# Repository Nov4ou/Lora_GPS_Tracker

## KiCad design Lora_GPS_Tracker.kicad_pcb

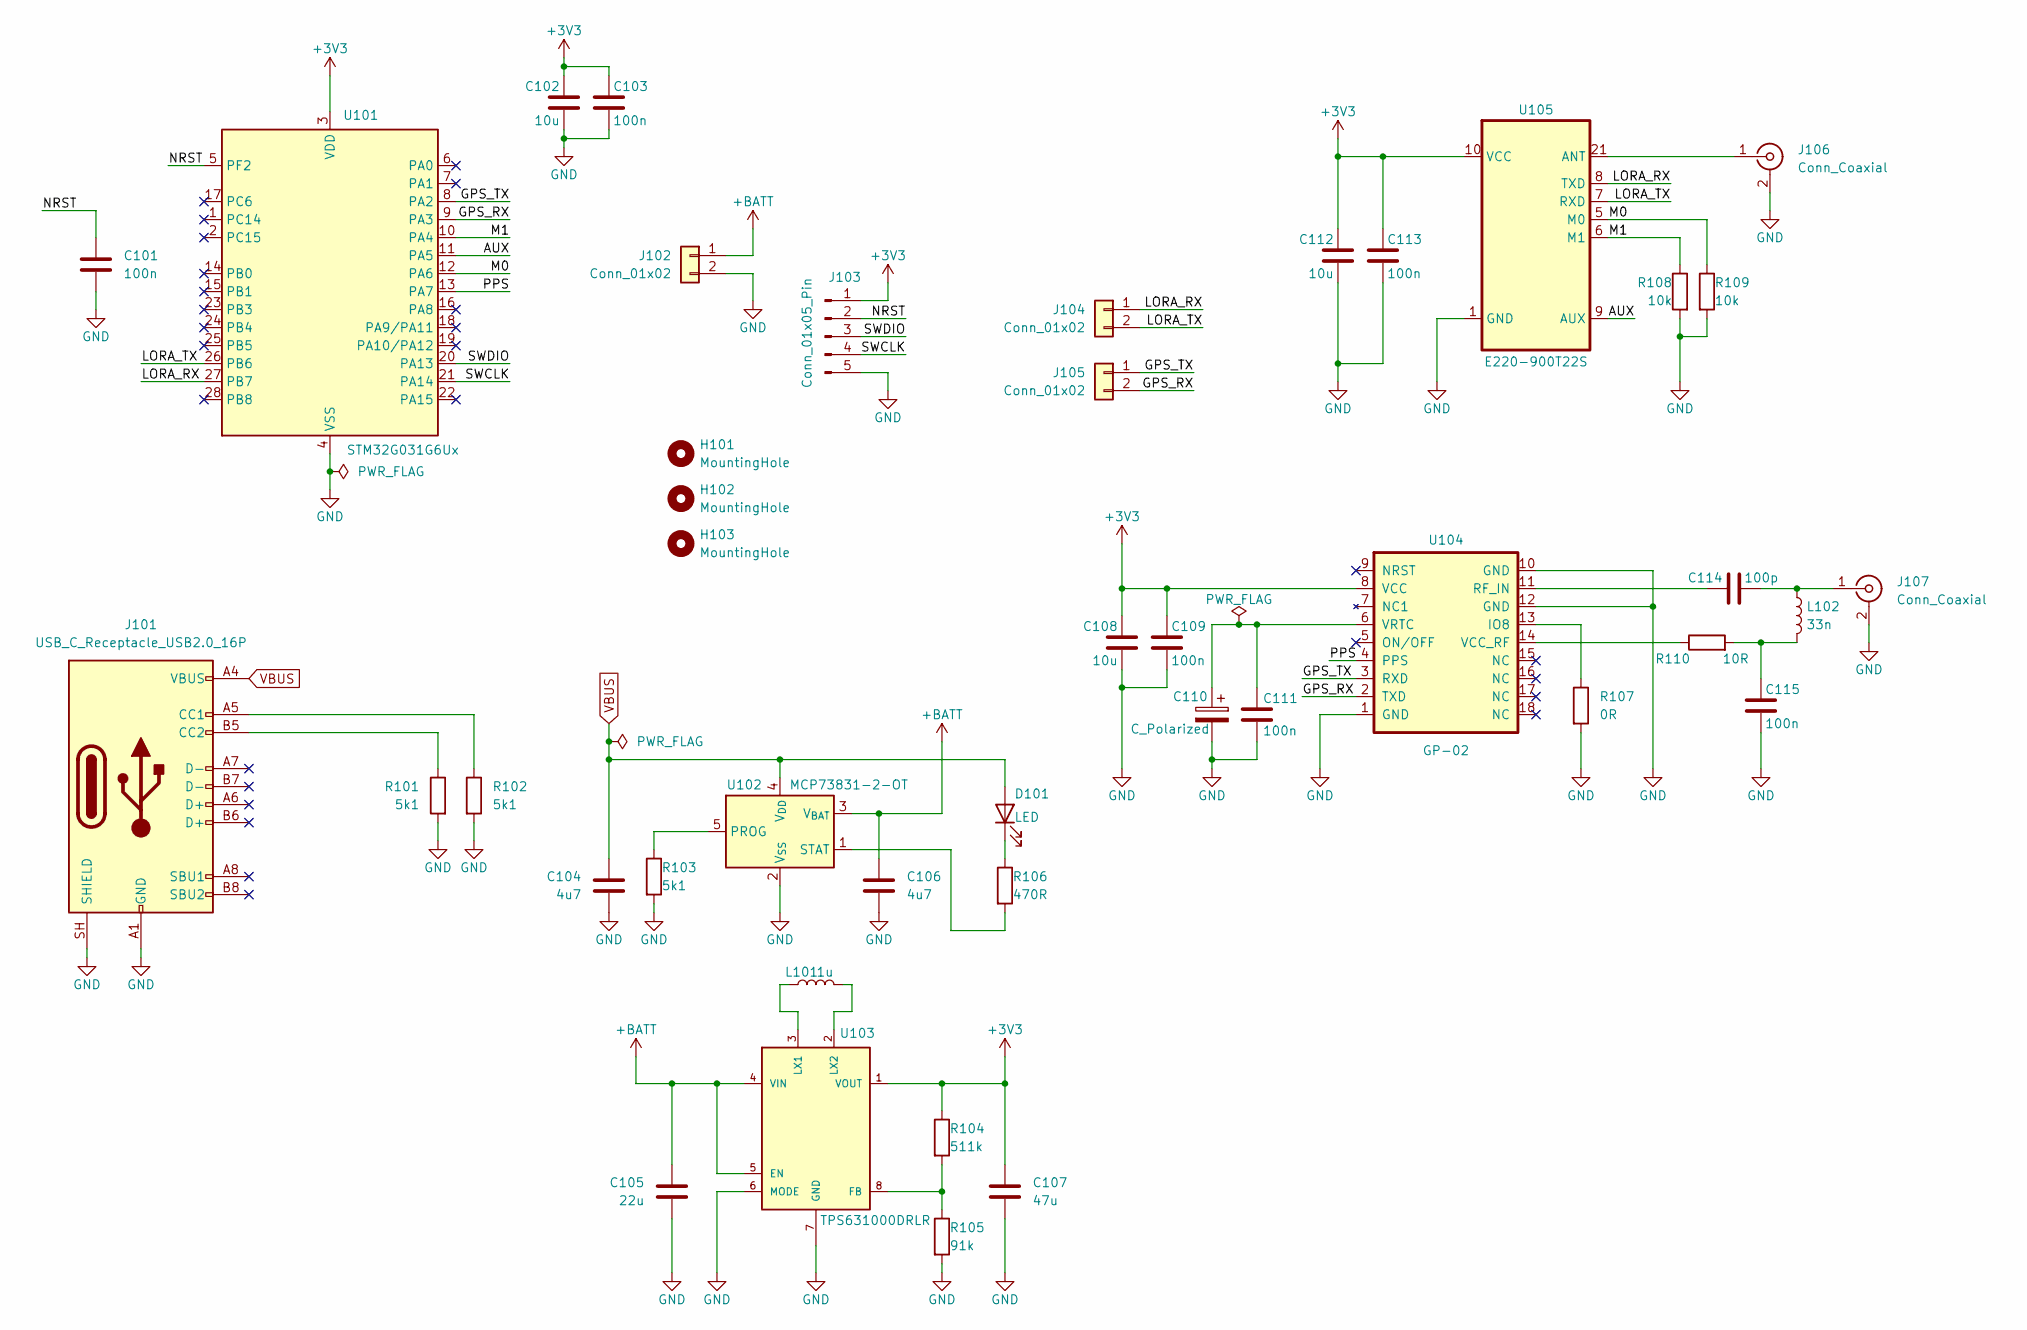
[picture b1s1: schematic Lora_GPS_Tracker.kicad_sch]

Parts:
C101, C103, C109, C111, C113, C115: 100n; C_0402_1005Metric
C102, C108, C112: 10u; C_0603_1608Metric
C104, C106: 4u7; C_0603_1608Metric
C105: 22u; C_0805_2012Metric
C107: 47u; C_0805_2012Metric
C110: C_Polarized; CAP-SMD_2P-L4.8-W4.8-TR
C114: 100p; C_0402_1005Metric
D101: LED; LED_0603_1608Metric
H101, H102, H103: MountingHole; MountingHole_2.2mm_M2
J101: USB_C_Receptacle_USB2.0_16P; USB_C_Receptacle_GCT_USB4105-xx-A_16P_TopMnt_Horizontal
J102: Conn_01x02; JST_PH_S2B-PH-K_1x02_P2.00mm_Horizontal
J103: Conn_01x05_Pin; PinHeader_1x05_P2.54mm_Vertical
J104, J105: Conn_01x02; PinHeader_1x02_P2.54mm_Vertical
J106: Conn_Coaxial; SMA_Samtec_SMA-J-P-H-ST-EM1_EdgeMount
J107: Conn_Coaxial; ANT-SMD_KH-IPEX-K501-29
L101: 1u; L_0603_1608Metric
L102: 33n; L_0603_1608Metric
R101, R102, R103: 5k1; R_0603_1608Metric
R104: 511k; R_0603_1608Metric
R105: 91k; R_0603_1608Metric
R106: 470R; R_0603_1608Metric
R107: 0R; R_0603_1608Metric
R108, R109: 10k; R_0603_1608Metric
R110: 10R; R_0603_1608Metric
U101: STM32G031G6Ux; QFN-28_4x4mm_P0.5mm
U102: MCP73831-2-OT; SOT-23-5
U103: TPS631000DRLR; PARTREV B
U104: GP-02; GP-02_FULL_PAD
U105: E220-900T22S; WIRELM-SMD_E220-900T22S

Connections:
+3V3: C102.1, C103.1, C107.1, C108.1, C109.1, C112.1, C113.1, J103.1, R104.1, U101.3 (VDD), U103.1 (VOUT), U104.8 (VCC), U105.10 (VCC)
+BATT: C105.1, C106.1, J102.1, U102.3 (V_{BAT}), U103.4 (VIN), U103.5 (EN)
/AUX: U101.11 (PA5), U105.9 (AUX)
/GPS_RX: J105.2, U101.9 (PA3), U104.2 (TXD)
/GPS_TX: J105.1, U101.8 (PA2), U104.3 (RXD)
/LORA_RX: J104.1, U101.27 (PB7), U105.8 (TXD)
/LORA_TX: J104.2, U101.26 (PB6), U105.7 (RXD)
/M0: R109.1, U101.12 (PA6), U105.5 (M0)
/M1: R108.1, U101.10 (PA4), U105.6 (M1)
/NRST: C101.1, J103.2, U101.5 (PF2)
/PPS: U101.13 (PA7), U104.4 (PPS)
/SWCLK: J103.4, U101.21 (PA14)
/SWDIO: J103.3, U101.20 (PA13)
GND: C101.2, C102.2, C103.2, C104.2, C105.2, C106.2, C107.2, C108.2, C109.2, C110.2, C111.2, C112.2, C113.2, C115.2, J101.A1 (GND), J101.A12 (GND), J101.B1 (GND), J101.B12 (GND), J101.SH (SHIELD), J102.2, J103.5, J106.2 (Ext), J107.2 (Ext), R101.2, R102.2, R103.2, R105.2, R107.2, R108.2, R109.2, U101.4 (VSS), U102.2 (V_{SS}), U103.6 (MODE), U103.7 (GND), U104.1 (GND), U104.10 (GND), U104.12 (GND), U105.1 (GND), U105.2 (GND), U105.3 (GND), U105.4 (GND), U105.11 (GND), U105.13 (GND), U105.19 (GND), U105.20 (GND), U105.22 (GND)
unnamed: C115.1, L102.2, R110.2
unnamed: D101.1 (K), R106.1
unnamed: J101.A5 (CC1), R102.1
unnamed: J101.B5 (CC2), R101.1
unnamed: J106.1 (In), U105.21 (ANT)
unnamed: C114.2, J107.1 (In), L102.1
unnamed: R103.1, U102.5 (PROG)
unnamed: R106.2, U102.1 (STAT)
unnamed: R104.2, R105.1, U103.8 (FB)
unnamed: L101.1, U103.3 (LX1)
unnamed: L101.2, U103.2 (LX2)
unnamed: R107.1, U104.13 (IO8)
unnamed: C114.1, U104.11 (RF_IN)
unnamed: R110.1, U104.14 (VCC_RF)
unnamed: C110.1, C111.1, U104.6 (VRTC)
VBUS: C104.1, D101.2 (A), J101.A4 (VBUS), J101.A9 (VBUS), J101.B4 (VBUS), J101.B9 (VBUS), U102.4 (V_{DD})

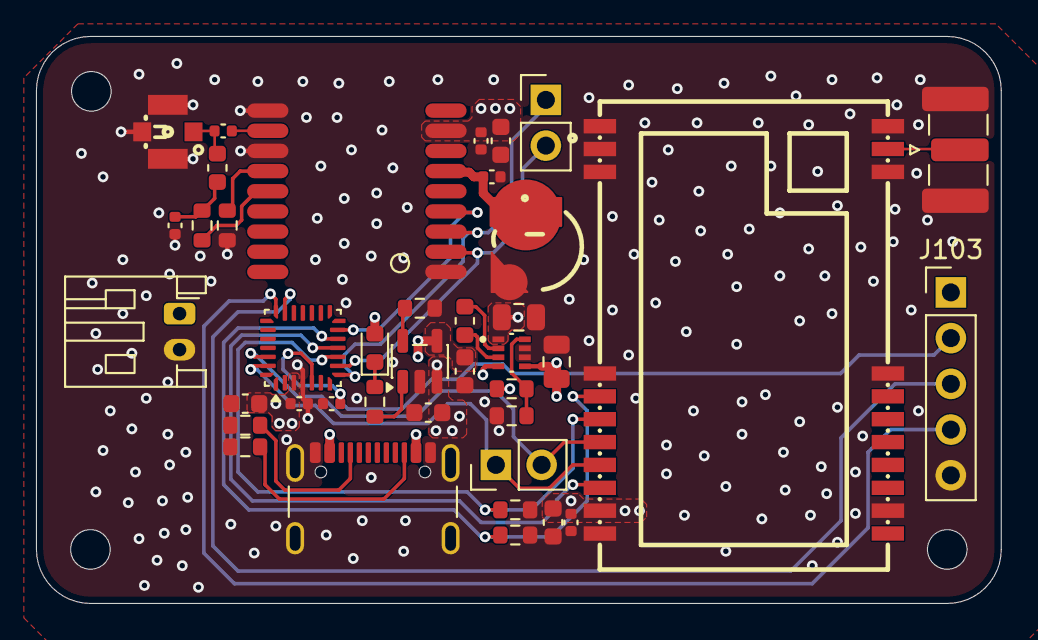
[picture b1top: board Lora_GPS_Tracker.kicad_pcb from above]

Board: 4 copper layers, 53.6 x 31.5 mm, 43 parts (0 on the bottom side), 30 nets.

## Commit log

2026-05-15 feat: init commit; finish basic power sch design
2026-05-20 feat: finish gps & lora sch design
2026-05-20 feat: finish battery & swd pins; need to assign mcu pinout
2026-05-21 feat: finish sch design
2026-05-27 feat: finish rough layout
2026-05-27 chore: add .gitignore
2026-05-27 feat: finish baisc layout
